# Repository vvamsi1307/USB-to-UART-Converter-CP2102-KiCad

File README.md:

# USB to UART Converter using CP2102

## Project Overview
This project is a compact USB to UART converter designed using KiCad.  
The board allows communication between a computer USB port and microcontrollers via UART.

## Features
• CP2102 USB to UART Bridge Controller  
• USB Micro Connector Interface  
• UART TX/RX Header Output  
• ESD Protection Diodes  
• Decoupling Capacitors for Stable Operation  
• 2-Layer PCB with Ground Plane  
• Compact PCB Layout  

## Applications
• Embedded System Debugging  
• Microcontroller Programming  
• Serial Communication Interface  
• IoT Development Boards  

## Tools Used
• KiCad – Schematic Design  
• KiCad – PCB Layout  
• KiCad – 3D Viewer  
• Gerber File Generation  

## Hardware Components
• CP2102 USB-UART Bridge  
• USB Micro Connector  
• ESD Protection Diode  
• Decoupling Capacitors  
• UART Pin Header  

## Files Included
• Schematic  
• PCB Layout  
• 3D Model  
• Gerber Files  

## Author
Anith Raja  
Electronics Engineer | Embedded Systems | PCB Design

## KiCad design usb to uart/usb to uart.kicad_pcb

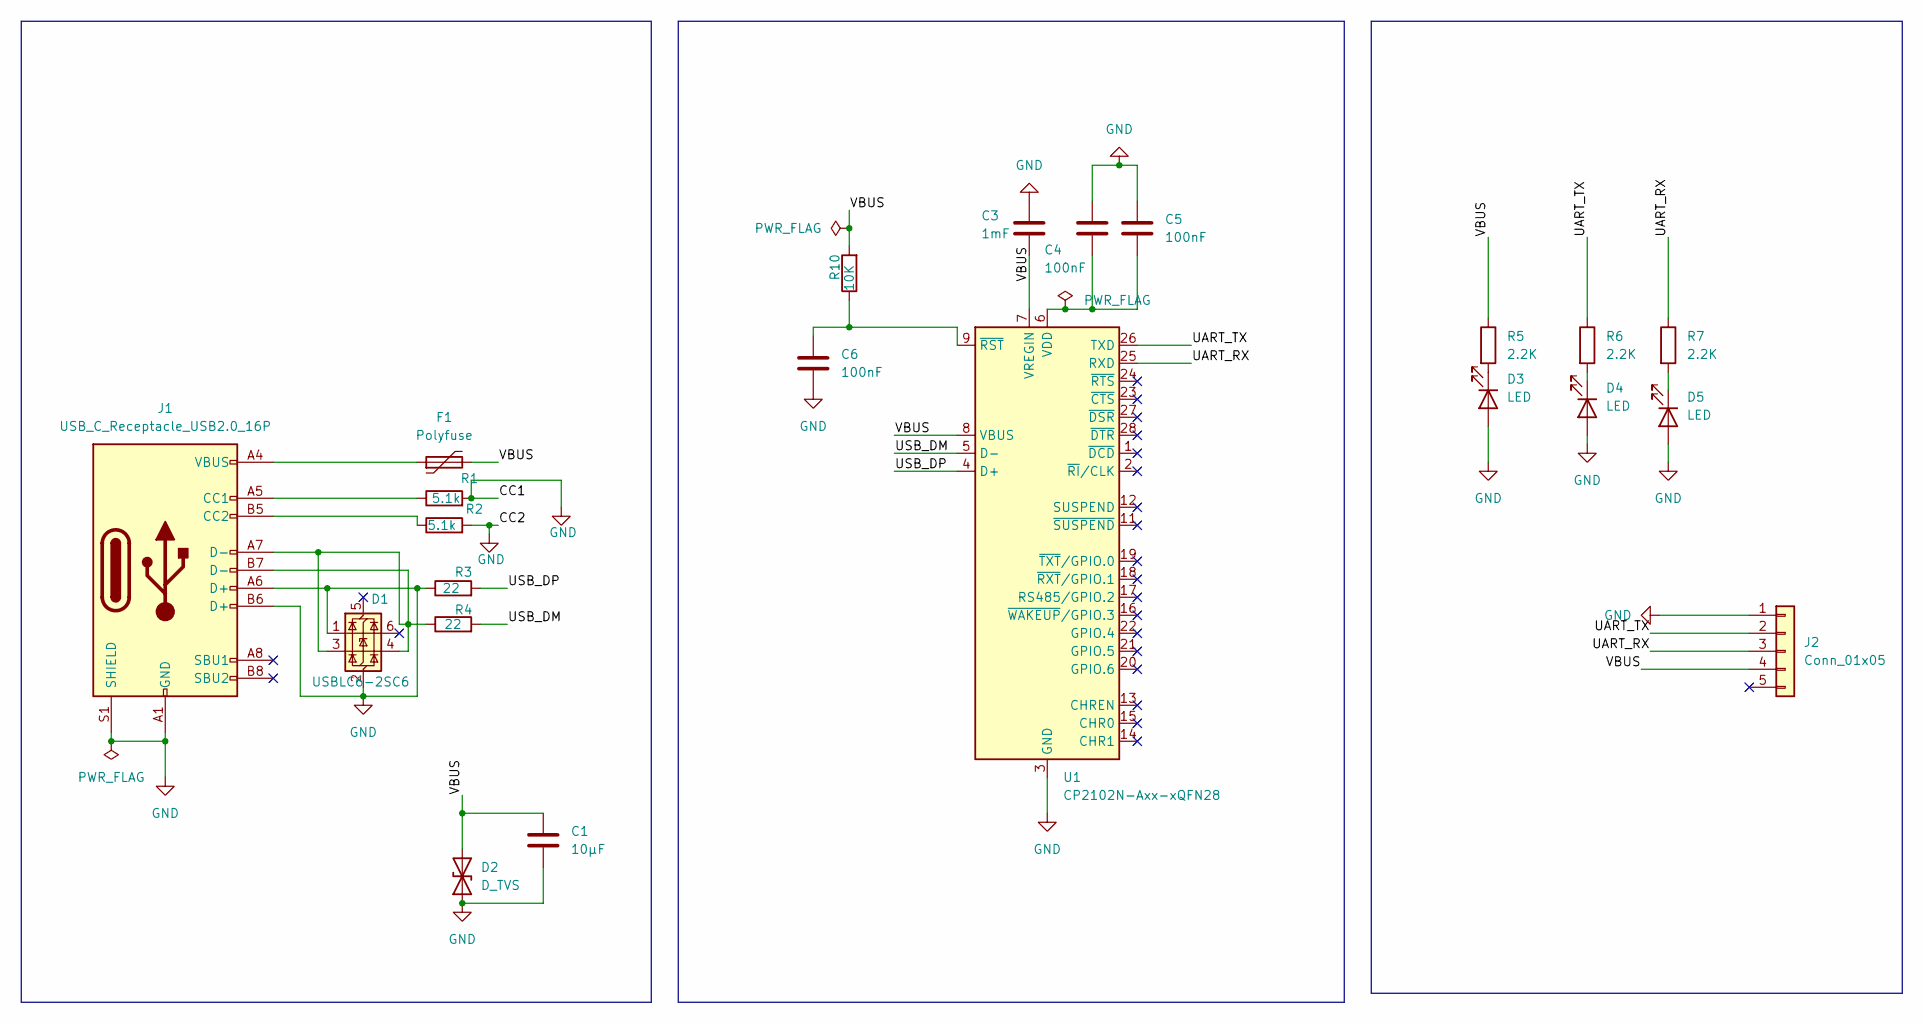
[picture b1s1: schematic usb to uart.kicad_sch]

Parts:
C1: 10µF; C_0603_1608Metric
C3: 1mF; C_0603_1608Metric
C4, C5, C6: 100nF; C_0603_1608Metric
D1: USBLC6-2SC6; SOT-23-6
D2: D_TVS; D_SOD-323
D3, D4, D5: LED; LED_0603_1608Metric
F1: Polyfuse; Fuse_1812_4532Metric
J1: USB_C_Receptacle_USB2.0_16P; USB_C_Receptacle_HRO_TYPE-C-31-M-12
J2: Conn_01x05; PinHeader_1x05_P2.54mm_Horizontal
R1, R2: 5.1k; R_0603_1608Metric
R3, R4: 22; R_0603_1608Metric
R5, R6, R7: 2.2K; R_0603_1608Metric
R10: 10K; R_0603_1608Metric
U1: CP2102N-Axx-xQFN28; QFN-28-1EP_5x5mm_P0.5mm_EP3.35x3.35mm

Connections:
/UART_RX: J2.3, R7.1, U1.25 (RXD)
/UART_TX: J2.2, R6.1, U1.26 (TXD)
/USB_DM: R4.2, U1.5 (D-)
/USB_DP: R3.2, U1.4 (D+)
/VBUS: C1.1, C3.2, D2.2 (A2), F1.2, J2.4, R5.1, R10.2, U1.7 (VREGIN), U1.8 (VBUS)
GND: C1.2, C3.1, C4.1, C5.1, C6.2, D1.1 (I/O1), D1.2 (GND), D2.1 (A1), D3.2 (A), D4.2 (A), D5.2 (A), J1.A1 (GND), J1.A6 (D+), J1.A12 (GND), J1.B1 (GND), J1.B6 (D+), J1.B12 (GND), J1.S1 (SHIELD), J2.1, R1.2, R2.2, R3.1, U1.3 (GND), U1.29 (GND)
unnamed: D1.3 (I/O2), D1.4 (I/O2), J1.A7 (D-), J1.B7 (D-), R4.1
unnamed: D3.1 (K), R5.2
unnamed: D4.1 (K), R6.2
unnamed: D5.1 (K), R7.2
unnamed: F1.1, J1.A4 (VBUS), J1.A9 (VBUS), J1.B4 (VBUS), J1.B9 (VBUS)
unnamed: J1.A5 (CC1), R1.1
unnamed: J1.B5 (CC2), R2.1
unnamed: C4.2, C5.2, U1.6 (VDD)
unnamed: C6.1, R10.1, U1.9 (~RST)

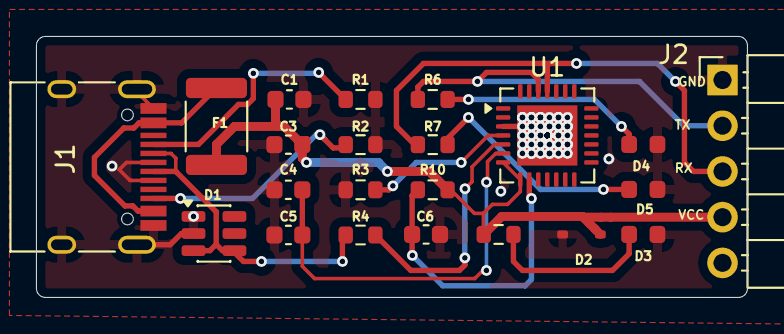
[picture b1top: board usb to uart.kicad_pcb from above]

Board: 2 copper layers, 39.5 x 14.5 mm, 22 parts (0 on the bottom side), 15 nets.

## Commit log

2026-03-10 updated files
